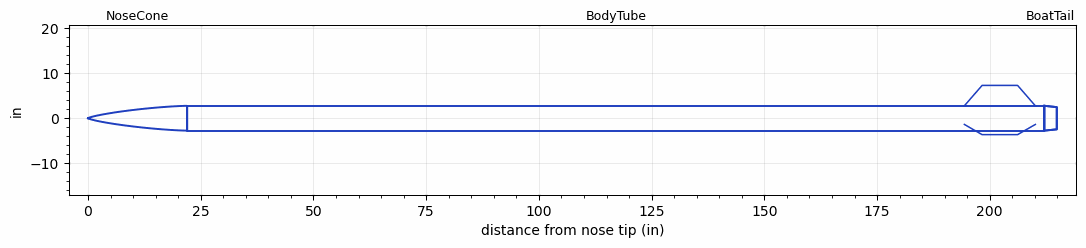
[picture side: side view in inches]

<RASAeroDocument>
 <FileVersion>2</FileVersion>
 <RocketDesign>
  <NoseCone>
   <Length>22</Length>
   <Diameter>5.5</Diameter>
   <Shape>Von Karman Ogive</Shape>
   <Location>0</Location>
  </NoseCone>
  <BodyTube>
   <Length>190.11</Length>
   <Diameter>5.5</Diameter>
   <Location>22</Location>
   <BoattailLength>2.75</BoattailLength>
   <BoattailRearDiameter>4.93</BoattailRearDiameter>
   <Fin>
    <Count>3</Count>
    <Chord>15.75</Chord>
    <Span>4.53</Span>
    <SweepDistance>3.94</SweepDistance>
    <TipChord>7.87</TipChord>
    <Thickness>0.28</Thickness>
    <LERadius>0.5</LERadius>
    <Location>17.75</Location>
    <AirfoilSection>Hexagonal</AirfoilSection>
    <FX1>0.5</FX1>
    <FX3>0.5</FX3>
   </Fin>
  </BodyTube>
  <BoatTail>
   <Length>2.75</Length>
   <Diameter>5.5</Diameter>
   <RearDiameter>4.93</RearDiameter>
   <Location>212.11</Location>
  </BoatTail>
  <Surface>Smooth (Zero Roughness)</Surface>
  <ModifiedBarrowman>False</ModifiedBarrowman>
  <Turbulence>False</Turbulence>
  <UseBooster1>False</UseBooster1>
  <UseBooster2>False</UseBooster2>
 </RocketDesign>
 <LaunchSite>
  <Altitude>0</Altitude>
  <Pressure>0</Pressure>
  <RodAngle>0</RodAngle>
  <RodLength>4</RodLength>
  <Temperature>74</Temperature>
  <WindSpeed>0</WindSpeed>
 </LaunchSite>
 <Recovery>
  <Altitude1>1000</Altitude1>
  <Altitude2>1000</Altitude2>
  <DeviceType1>None</DeviceType1>
  <DeviceType2>None</DeviceType2>
  <Event1>False</Event1>
  <Event2>False</Event2>
  <Size1>1</Size1>
  <Size2>1</Size2>
  <EventType1>None</EventType1>
  <EventType2>None</EventType2>
  <CD1>1.33</CD1>
  <CD2>1.33</CD2>
 </Recovery>
 <SimulationList>
  <Simulation>
   <SustainerEngine>Quasar  (UTAT)</SustainerEngine>
   <SustainerLaunchWt>136.44</SustainerLaunchWt>
   <SustainerCG>0</SustainerCG>
   <SustainerIgnitionDelay>0</SustainerIgnitionDelay>
   <Booster1SeparationDelay>0</Booster1SeparationDelay>
   <Booster1IgnitionDelay>0</Booster1IgnitionDelay>
   <IncludeBooster1>False</IncludeBooster1>
   <Booster2Delay>0</Booster2Delay>
   <IncludeBooster2>False</IncludeBooster2>
  </Simulation>
 </SimulationList>
</RASAeroDocument>
